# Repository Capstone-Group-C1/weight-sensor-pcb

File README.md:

# weight-sensor-pcb
Converts Load Cell(s) analog signal into CAN signal

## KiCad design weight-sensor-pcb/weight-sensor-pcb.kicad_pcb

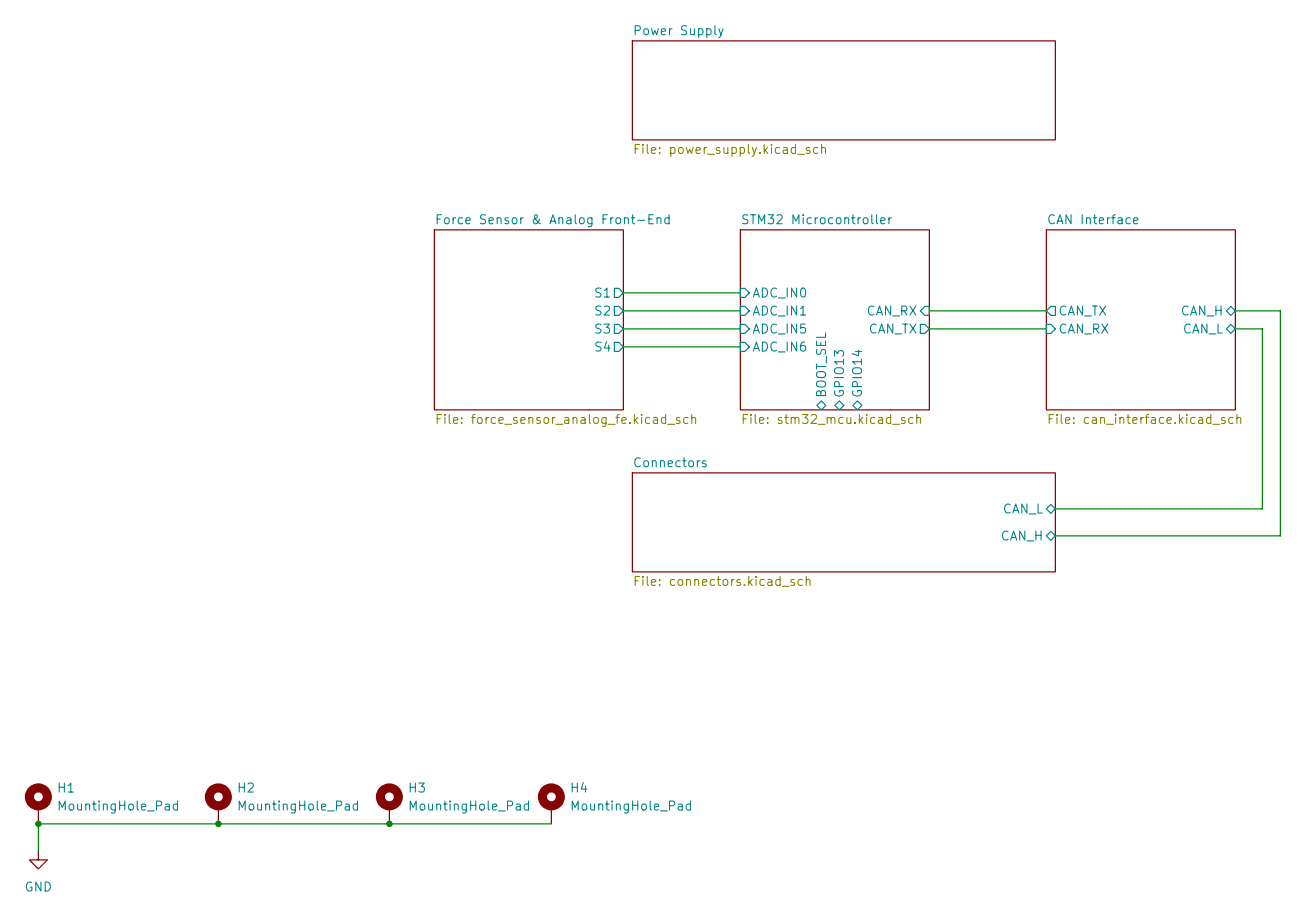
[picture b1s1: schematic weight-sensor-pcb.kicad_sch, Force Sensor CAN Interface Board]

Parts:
H1, H2, H3, H4: MountingHole_Pad; MountingHole_2.2mm_M2_Pad_Via

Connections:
GND: H1.1, H2.1, H3.1, H4.1; also elsewhere on the board

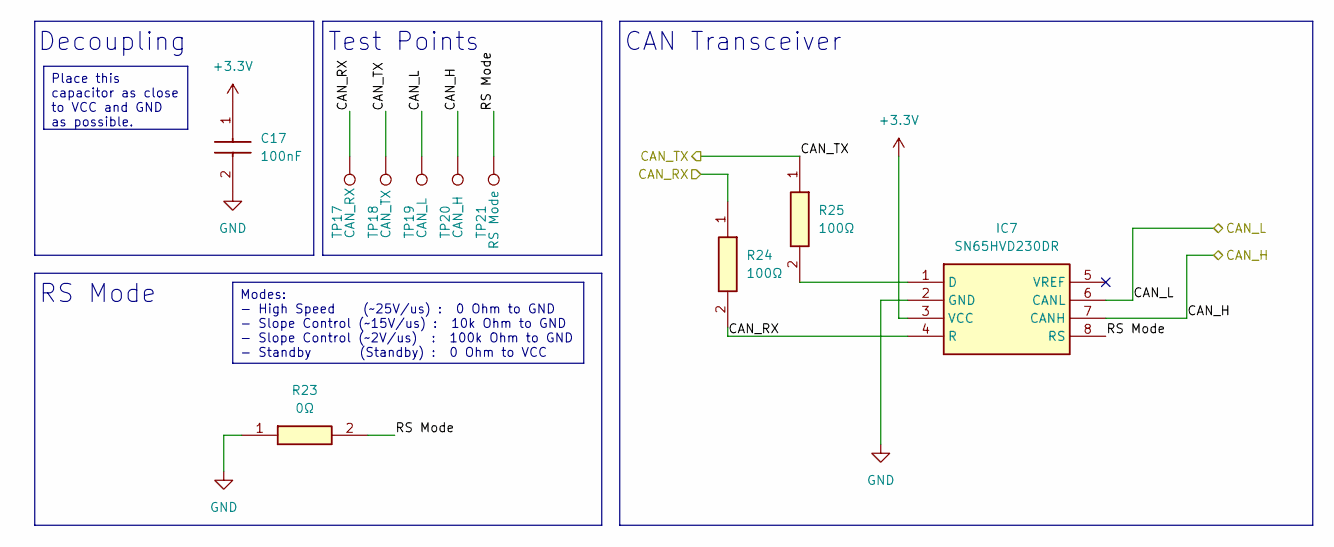
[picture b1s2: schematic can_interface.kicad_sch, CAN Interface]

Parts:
C17: 100nF; CAPC1005X70N; Manufacturer_Part_Number GRM155R70J104KA01D; Mouser Part Number 81-GRM155R70J104KA1D
IC7: SN65HVD230DR; SOT127P600X175-8N; Mouser Part Number 595-SN65HVD230DR
R23: 0Ω; RESC1608X55N; Manufacturer_Part_Number RC0603JR-070RL; Mouser Part Number 603-RC0603JR-070RL
R24, R25: 100Ω; RESC1608X55N; Manufacturer_Part_Number RC0603FR-07100RL; Mouser Part Number 603-RC0603FR-07100RL
TP17: CAN_RX; TestPoint_Pad_D1.5mm
TP18: CAN_TX; TestPoint_Pad_D1.5mm
TP19: CAN_L; TestPoint_Pad_D1.5mm
TP20: CAN_H; TestPoint_Pad_D1.5mm
TP21: RS Mode; TestPoint_Pad_D1.5mm

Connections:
+3.3V: C17.1, IC7.3 (VCC); also elsewhere on the board
/CAN Interface/CAN_H: IC7.7 (CANH), TP20.1; also elsewhere on the board
/CAN Interface/CAN_L: IC7.6 (CANL), TP19.1; also elsewhere on the board
/CAN Interface/CAN_RX: IC7.4 (R), R24.1, R24.2, TP17.1; also elsewhere on the board
/CAN Interface/CAN_TX: R25.1, TP18.1; also elsewhere on the board
/CAN Interface/RS Mode: IC7.8 (RS), R23.2, TP21.1
GND: C17.2, IC7.2 (GND), R23.1; also elsewhere on the board
unnamed: IC7.1 (D), R25.2

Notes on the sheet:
Decoupling
Test Points
CAN Transceiver
RS Mode
Modes: - High Speed (~25V/us) : 0 Ohm to GND - Slope Control (~15V/us) : 10k Ohm to GND - Slope Control (~2V/us) : 100k Ohm to GND - Standby (Standby) : 0 Ohm to VCC
Place this capacitor as close to VCC and GND as possible.

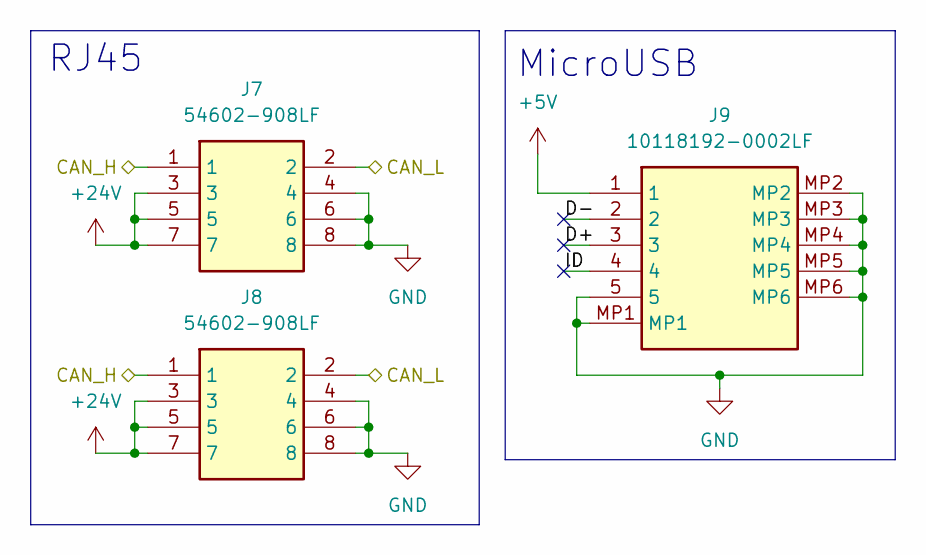
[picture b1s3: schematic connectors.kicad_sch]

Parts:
J7, J8: 54602-908LF; 54602908LF; Manufacturer_Part_Number 54602-908LF
J9: 10118192-0002LF; 101181920002LF; Manufacturer_Part_Number 10118192-0002LF

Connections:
+5V: J9.1; also elsewhere on the board
+24V: J7.3, J7.5, J7.7, J8.3, J8.5, J8.7; also elsewhere on the board
/CAN Interface/CAN_H: J7.1, J8.1; also elsewhere on the board
/CAN Interface/CAN_L: J7.2, J8.2; also elsewhere on the board
/Connectors/D+: J9.3
/Connectors/D-: J9.2
/Connectors/ID: J9.4
GND: J7.4, J7.6, J7.8, J8.4, J8.6, J8.8, J9.5, J9.MP1, J9.MP2, J9.MP3, J9.MP4, J9.MP5, J9.MP6; also elsewhere on the board

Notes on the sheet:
MicroUSB
RJ45

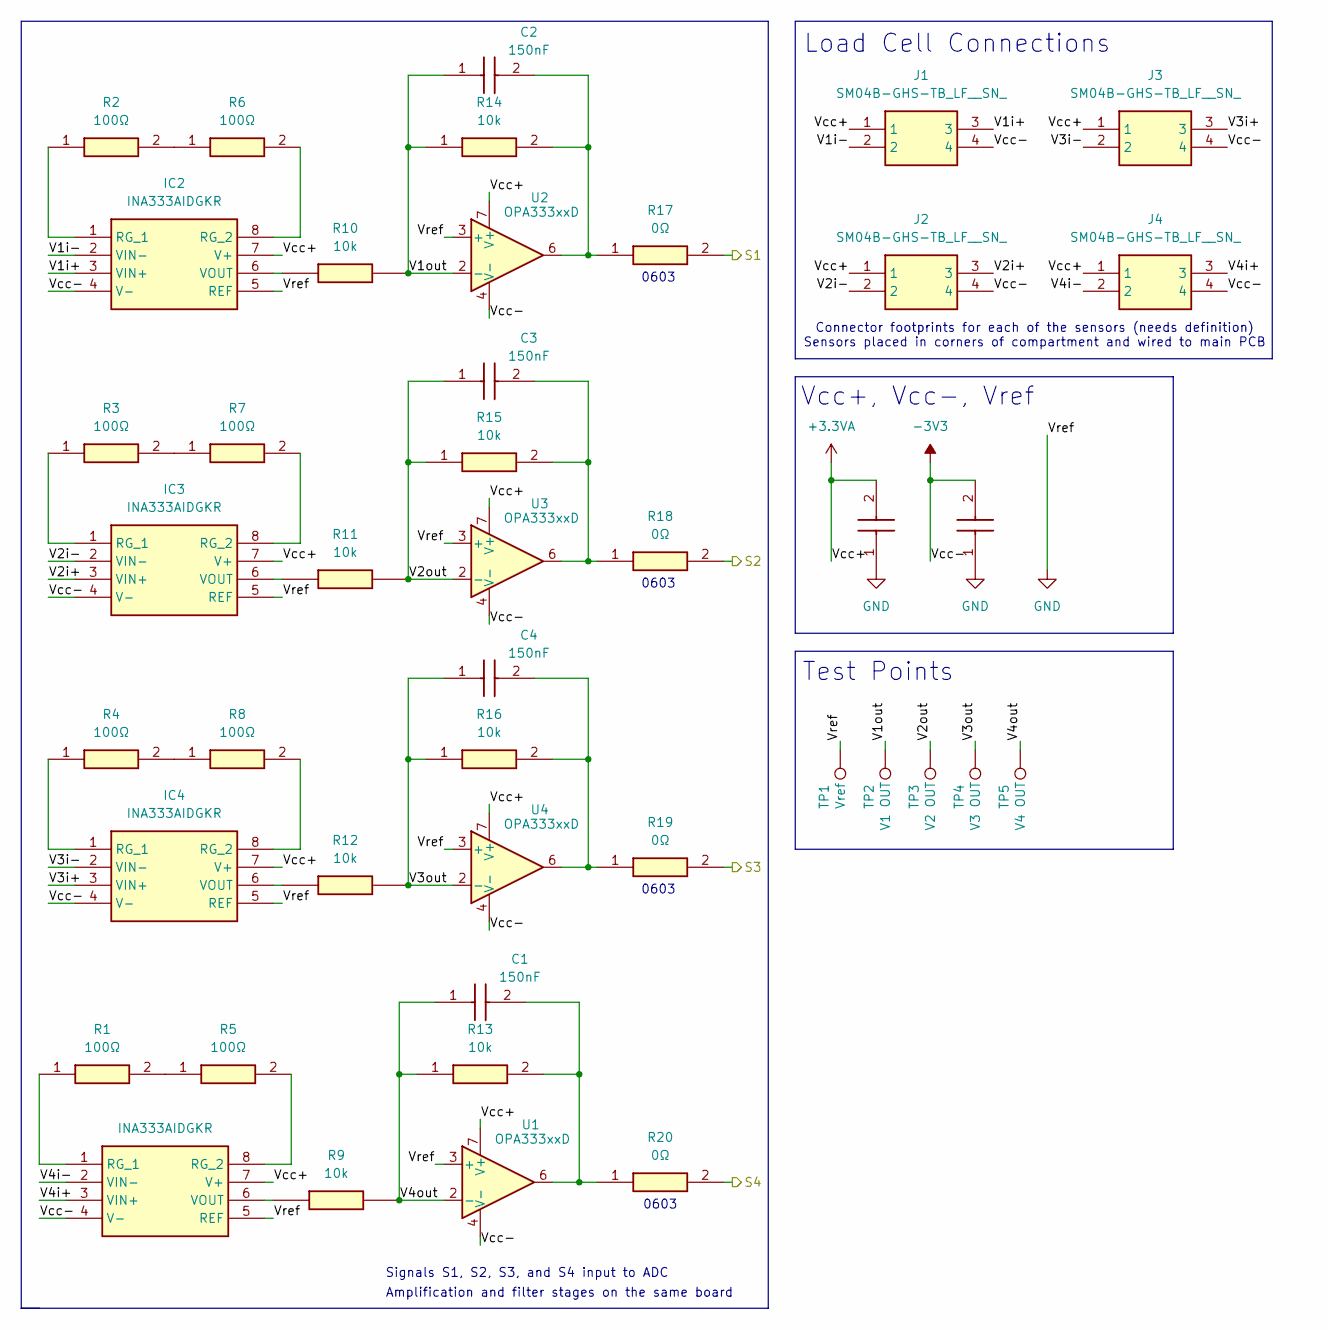
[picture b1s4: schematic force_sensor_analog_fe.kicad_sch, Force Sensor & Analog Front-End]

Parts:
C1, C2, C3, C4: 150nF; C4532_Commercial; Manufacturer_Part_Number C4532C0G1H154J250KA
C5, C6: 0.1uF; CAPC0603X33N; Mouser Part Number 81-GRM33C71C104KE14D
IC1, IC2, IC3, IC4: INA333AIDGKR; SOP65P490X110-8N; Manufacturer_Part_Number INA333AIDGKR; Mouser Part Number 595-INA333AIDGKR
J1, J2, J3, J4: SM04B-GHS-TB_LF__SN_; SM04B-GHS-TB; Mouser Part Number N/A
R1, R2, R3, R4, R5, R6, R7, R8: 100Ω; RESC1608X55N; Manufacturer_Part_Number RC0603FR-07100RL; Mouser Part Number 603-RC0603FR-07100RL
R9, R10, R11, R12, R13, R14, R15, R16: 10k; RESC1608X55N; Manufacturer_Part_Number RMCF0603FT10K0; Mouser Part Number 708-RMCF0603FT10K0
R17, R18, R19, R20: 0Ω; RESC1608X55N; Manufacturer_Part_Number RC0603JR-070RL; Mouser Part Number 603-RC0603JR-070RL
TP1: Vref; TestPoint_Pad_D1.5mm
TP2: V1 OUT; TestPoint_Pad_D1.5mm
TP3: V2 OUT; TestPoint_Pad_D1.5mm
TP4: V3 OUT; TestPoint_Pad_D1.5mm
TP5: V4 OUT; TestPoint_Pad_D1.5mm
U1, U2, U3, U4: OPA333xxD; SOIC-8_3.9x4.9mm_P1.27mm

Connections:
+3.3VA: C5.2, IC1.7 (V+), IC2.7 (V+), IC3.7 (V+), IC4.7 (V+), J1.1, J2.1, J3.1, J4.1, U1.7 (V+), U2.7 (V+), U3.7 (V+), U4.7 (V+); also elsewhere on the board
-3V3: C6.2, IC1.4 (V-), IC2.4 (V-), IC3.4 (V-), IC4.4 (V-), J1.4, J2.4, J3.4, J4.4, U1.4 (V-), U2.4 (V-), U3.4 (V-), U4.4 (V-); also elsewhere on the board
/Force Sensor & Analog Front-End/V1i+: IC2.3 (VIN+), J1.3
/Force Sensor & Analog Front-End/V1i-: IC2.2 (VIN-), J1.2
/Force Sensor & Analog Front-End/V1out: C2.1, R10.2, R14.1, TP2.1, U2.2 (-)
/Force Sensor & Analog Front-End/V2i+: IC3.3 (VIN+), J2.3
/Force Sensor & Analog Front-End/V2i-: IC3.2 (VIN-), J2.2
/Force Sensor & Analog Front-End/V2out: C3.1, R11.2, R15.1, TP3.1, U3.2 (-)
/Force Sensor & Analog Front-End/V3i+: IC4.3 (VIN+), J3.3
/Force Sensor & Analog Front-End/V3i-: IC4.2 (VIN-), J3.2
/Force Sensor & Analog Front-End/V3out: C4.1, R12.2, R16.1, TP4.1, U4.2 (-)
/Force Sensor & Analog Front-End/V4i+: IC1.3 (VIN+), J4.3
/Force Sensor & Analog Front-End/V4i-: IC1.2 (VIN-), J4.2
/Force Sensor & Analog Front-End/V4out: C1.1, R9.2, R13.1, TP5.1, U1.2 (-)
/STM32 Microcontroller/ADC_IN0: R17.2; also elsewhere on the board
/STM32 Microcontroller/ADC_IN1: R18.2; also elsewhere on the board
/STM32 Microcontroller/ADC_IN5: R19.2; also elsewhere on the board
/STM32 Microcontroller/ADC_IN6: R20.2; also elsewhere on the board
GND: C5.1, C6.1, IC1.5 (REF), IC2.5 (REF), IC3.5 (REF), IC4.5 (REF), TP1.1, U1.3 (+), U2.3 (+), U3.3 (+), U4.3 (+); also elsewhere on the board
unnamed: C1.2, R13.2, R20.1, U1.6
unnamed: C2.2, R14.2, R17.1, U2.6
unnamed: C3.2, R15.2, R18.1, U3.6
unnamed: C4.2, R16.2, R19.1, U4.6
unnamed: IC1.1 (RG_1), R1.1
unnamed: IC1.8 (RG_2), R5.2
unnamed: IC1.6 (VOUT), R9.1
unnamed: IC2.1 (RG_1), R2.1
unnamed: IC2.8 (RG_2), R6.2
unnamed: IC2.6 (VOUT), R10.1
unnamed: IC3.1 (RG_1), R3.1
unnamed: IC3.8 (RG_2), R7.2
unnamed: IC3.6 (VOUT), R11.1
unnamed: IC4.1 (RG_1), R4.1
unnamed: IC4.8 (RG_2), R8.2
unnamed: IC4.6 (VOUT), R12.1
unnamed: R1.2, R5.1
unnamed: R2.2, R6.1
unnamed: R3.2, R7.1
unnamed: R4.2, R8.1

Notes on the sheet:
Load Cell Connections
0603
Signals S1, S2, S3, and S4 input to ADC
Amplification and filter stages on the same board
Connector footprints for each of the sensors (needs definition) Sensors placed in corners of compartment and wired to main PCB
Test Points
Vcc+, Vcc-, Vref

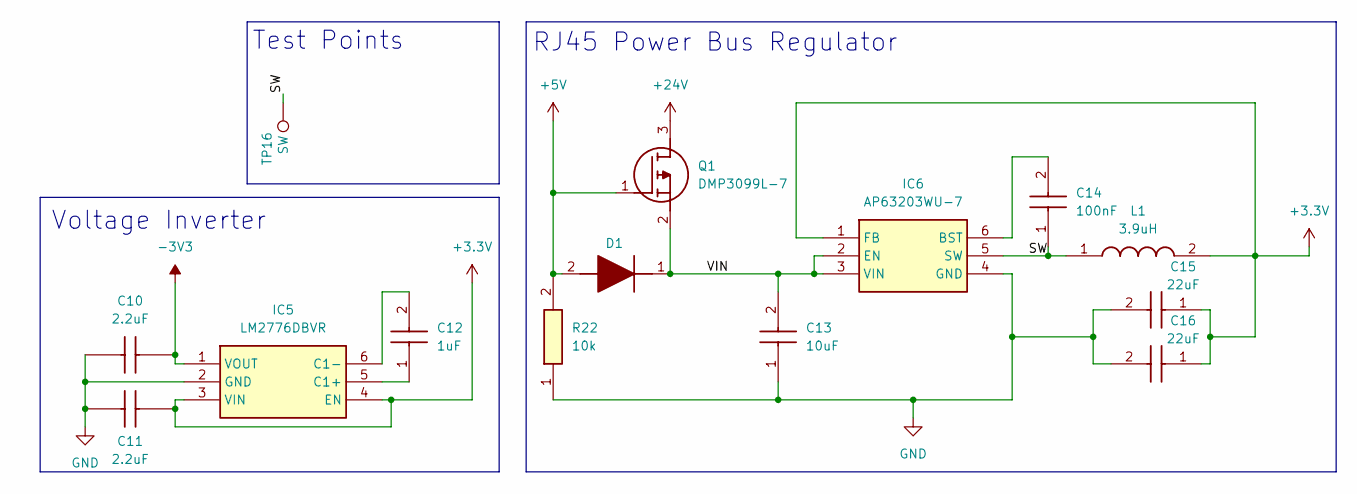
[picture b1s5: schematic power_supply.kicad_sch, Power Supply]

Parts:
C10, C11: 2.2uF; CAPC1608X90N; Mouser Part Number 81-GRM1885C1H222JA01
C12: 1uF; CAPC1005X70N; Manufacturer_Part_Number GRM155R70J105KA12D; Mouser Part Number 81-GRM155R70J105KA2D
C13: 10uF; CAPC2012X145N; Mouser Part Number 81-GRM21BR61E106KA3K
C14: 100nF; CAPC1005X70N; Manufacturer_Part_Number GRM155R70J104KA01D; Mouser Part Number 81-GRM155R70J104KA1D
C15, C16: 22uF; CAPC3216X190N; Mouser Part Number 963-TMK316BBJ226ML-T
D1: BAT30KFILM; SODFL1608X70N; Manufacturer_Part_Number BAT30KFILM; Mouser Part Number 511-BAT30KFILM
IC5: LM2776DBVR; SOT95P280X145-6N; Manufacturer_Part_Number LM2776DBVR; Mouser Part Number 595-LM2776DBVR
IC6: AP63203WU-7; AP63203WU7; Manufacturer_Part_Number AP63203WU-7; Mouser Part Number 621-AP63203WU-7
L1: 3.9uH; ASPI0628150MT1; Mouser Part Number 815-ASPI-0628-3R9MT1
Q1: DMP3099L-7; SOT96P240X115-3N; Manufacturer_Part_Number DMP3099L-7; Mouser Part Number 621-DMP3099L-7
R22: 10k; RESC1608X55N; Manufacturer_Part_Number RMCF0603FT10K0; Mouser Part Number 708-RMCF0603FT10K0
TP16: SW; TestPoint_Pad_D1.5mm

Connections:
+3.3V: C11.1, C15.1, C16.1, IC5.3 (VIN), IC5.4 (EN), IC6.1 (FB), L1.2; also elsewhere on the board
+5V: D1.2 (A), Q1.1 (G), R22.2; also elsewhere on the board
+24V: Q1.3 (D); also elsewhere on the board
-3V3: C10.1, IC5.1 (VOUT); also elsewhere on the board
/Power Supply/SW: C14.1, IC6.5 (SW), L1.1, TP16.1
/Power Supply/VIN: C13.2, D1.1 (K), IC6.2 (EN), IC6.3 (VIN), Q1.2 (S)
GND: C10.2, C11.2, C13.1, C15.2, C16.2, IC5.2 (GND), IC6.4 (GND), R22.1; also elsewhere on the board
unnamed: C12.1, IC5.5 (C1+)
unnamed: C12.2, IC5.6 (C1-)
unnamed: C14.2, IC6.6 (BST)

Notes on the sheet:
RJ45 Power Bus Regulator
Test Points
Voltage Inverter

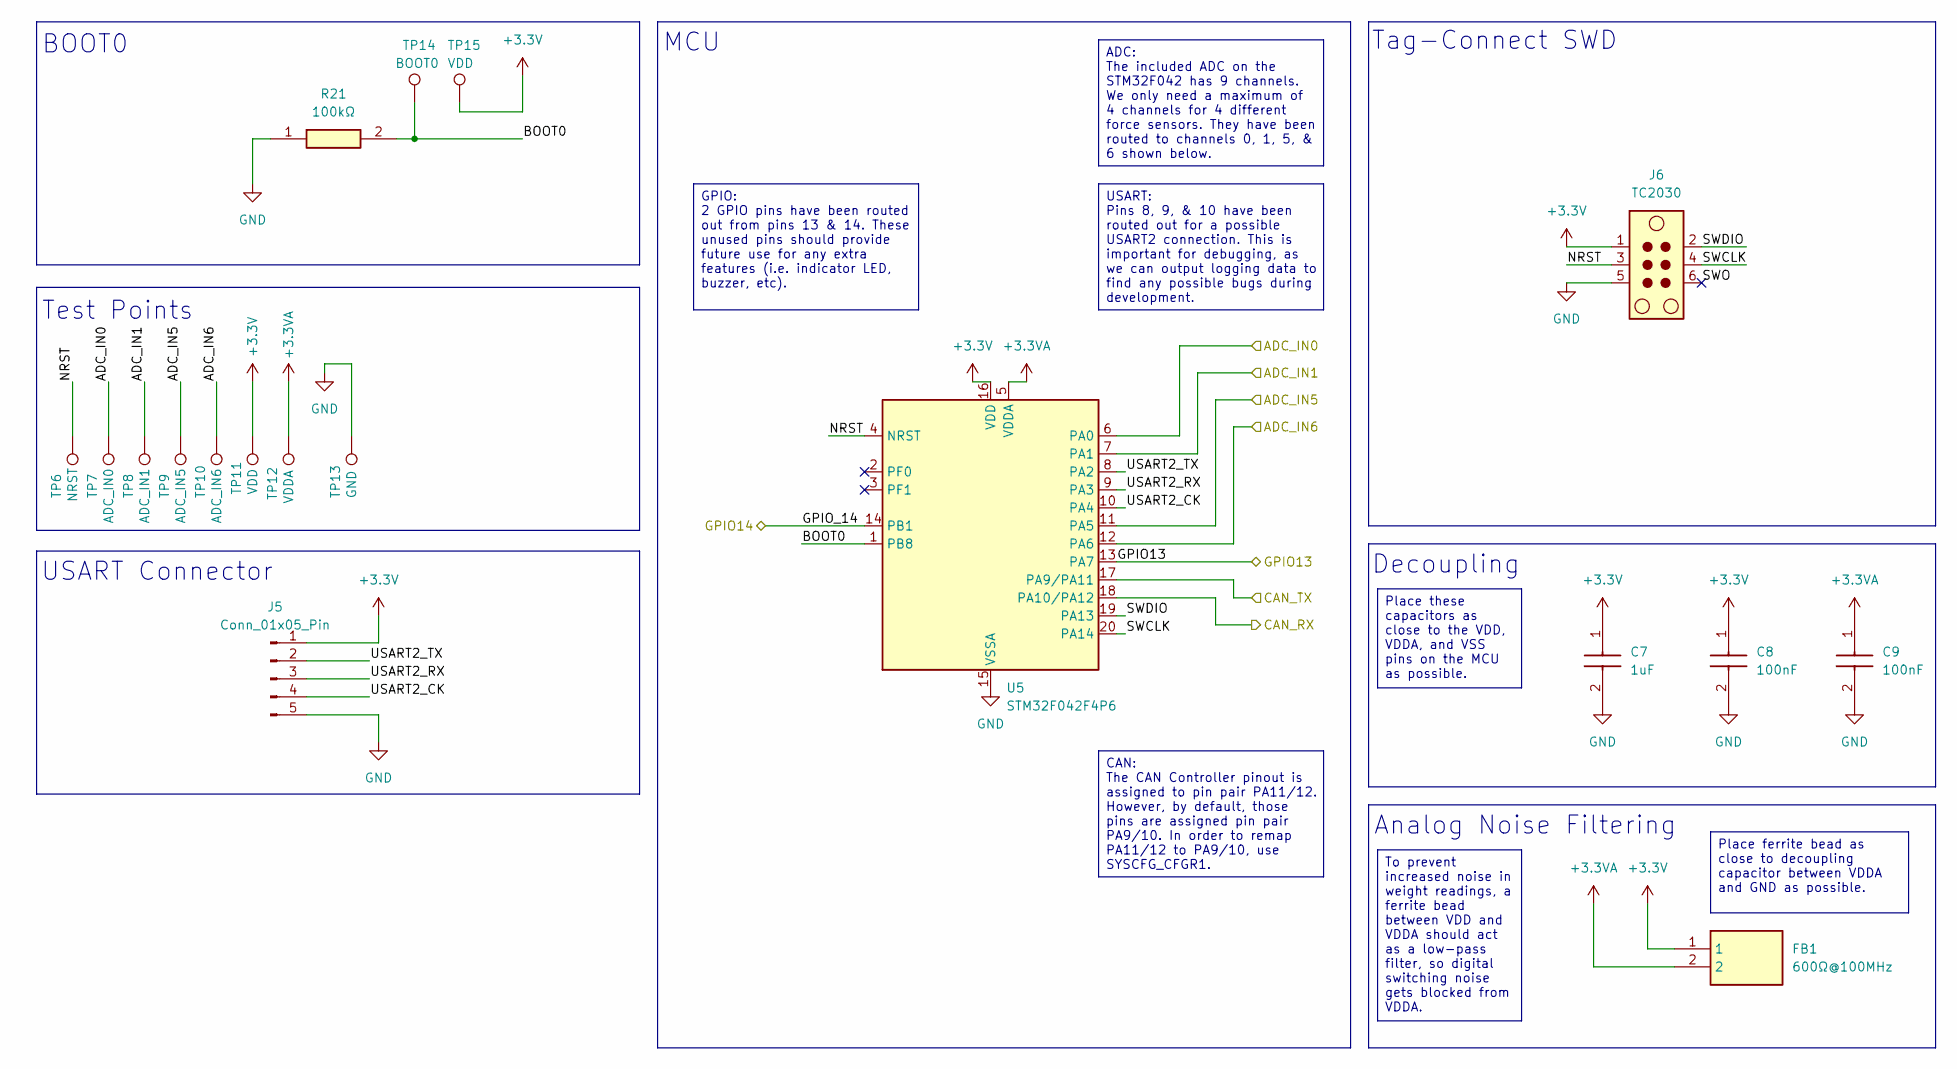
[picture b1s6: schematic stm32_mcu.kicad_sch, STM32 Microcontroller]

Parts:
C7: 1uF; CAPC1005X70N; Manufacturer_Part_Number GRM155R70J105KA12D; Mouser Part Number 81-GRM155R70J105KA2D
C8, C9: 100nF; CAPC1005X70N; Manufacturer_Part_Number GRM155R70J104KA01D; Mouser Part Number 81-GRM155R70J104KA1D
FB1: 600Ω@100MHz; NFZ15SG152SN10B; Manufacturer_Part_Number BLM15AG601SN1D; Mouser Part Number 81-BLM15AG601SN1D
J5: Conn_01x05_Pin; PinHeader_1x05_P1.27mm_Vertical
J6: TC2030; Tag-Connect_TC2030-IDC-NL_2x03_P1.27mm_Vertical
R21: 100kΩ; RESC1005X40N; Manufacturer_Part_Number RC0402FR-07100KL
TP6: NRST; TestPoint_Pad_D1.5mm
TP7: ADC_IN0; TestPoint_Pad_D1.5mm
TP8: ADC_IN1; TestPoint_Pad_D1.5mm
TP9: ADC_IN5; TestPoint_Pad_D1.5mm
TP10: ADC_IN6; TestPoint_Pad_D1.5mm
TP11, TP15: VDD; TestPoint_Pad_D1.5mm
TP12: VDDA; TestPoint_Pad_D1.5mm
TP13: GND; TestPoint_Pad_D1.5mm
TP14: BOOT0; TestPoint_Pad_D1.5mm
U5: STM32F042F4P6; TSSOP-20_4.4x6.5mm_P0.65mm

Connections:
+3.3V: C7.1, C8.1, FB1.1, J5.1, J6.1, TP11.1, TP15.1, U5.16 (VDD); also elsewhere on the board
+3.3VA: C9.1, FB1.2, TP12.1, U5.5 (VDDA); also elsewhere on the board
/CAN Interface/CAN_RX: U5.17 (PA9/PA11); also elsewhere on the board
/CAN Interface/CAN_TX: U5.18 (PA10/PA12); also elsewhere on the board
/STM32 Microcontroller/ADC_IN0: TP7.1, U5.6 (PA0); also elsewhere on the board
/STM32 Microcontroller/ADC_IN1: TP8.1, U5.7 (PA1); also elsewhere on the board
/STM32 Microcontroller/ADC_IN5: TP9.1, U5.11 (PA5); also elsewhere on the board
/STM32 Microcontroller/ADC_IN6: TP10.1, U5.12 (PA6); also elsewhere on the board
/STM32 Microcontroller/BOOT0: R21.2, TP14.1, U5.1 (PB8)
/STM32 Microcontroller/GPIO13: U5.13 (PA7)
/STM32 Microcontroller/GPIO_14: U5.14 (PB1)
/STM32 Microcontroller/NRST: J6.3, TP6.1, U5.4 (NRST)
/STM32 Microcontroller/SWCLK: J6.4, U5.20 (PA14)
/STM32 Microcontroller/SWDIO: J6.2, U5.19 (PA13)
/STM32 Microcontroller/SWO: J6.6
/STM32 Microcontroller/USART2_CK: J5.4, U5.10 (PA4)
/STM32 Microcontroller/USART2_RX: J5.3, U5.9 (PA3)
/STM32 Microcontroller/USART2_TX: J5.2, U5.8 (PA2)
GND: C7.2, C8.2, C9.2, J5.5, J6.5, R21.1, TP13.1, U5.15 (VSSA); also elsewhere on the board

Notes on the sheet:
Analog Noise Filtering
Test Points
MCU
BOOT0
USART Connector
Decoupling
Tag-Connect SWD
ADC: The included ADC on the STM32F042 has 9 channels. We only need a maximum of 4 channels for 4 different force sensors. They have been routed to channels 0, 1, 5, & 6 shown below.
Place these capacitors as close to the VDD, VDDA, and VSS pins on the MCU as possible.
USART: Pins 8, 9, & 10 have been routed out for a possible USART2 connection. This is important for debugging, as we can output logging data to find any possible bugs during development.
GPIO: 2 GPIO pins have been routed out from pins 13 & 14. These unused pins should provide future use for any extra features (i.e. indicator LED, buzzer, etc).
CAN: The CAN Controller pinout is assigned to pin pair PA11/12. However, by default, those pins are assigned pin pair PA9/10. In order to remap PA11/12 to PA9/10, use SYSCFG_CFGR1.
To prevent increased noise in weight readings, a ferrite bead between VDD and VDDA should act as a low-pass filter, so digital switching noise gets blocked from VDDA.
Place ferrite bead as close to decoupling capacitor between VDDA and GND as possible.

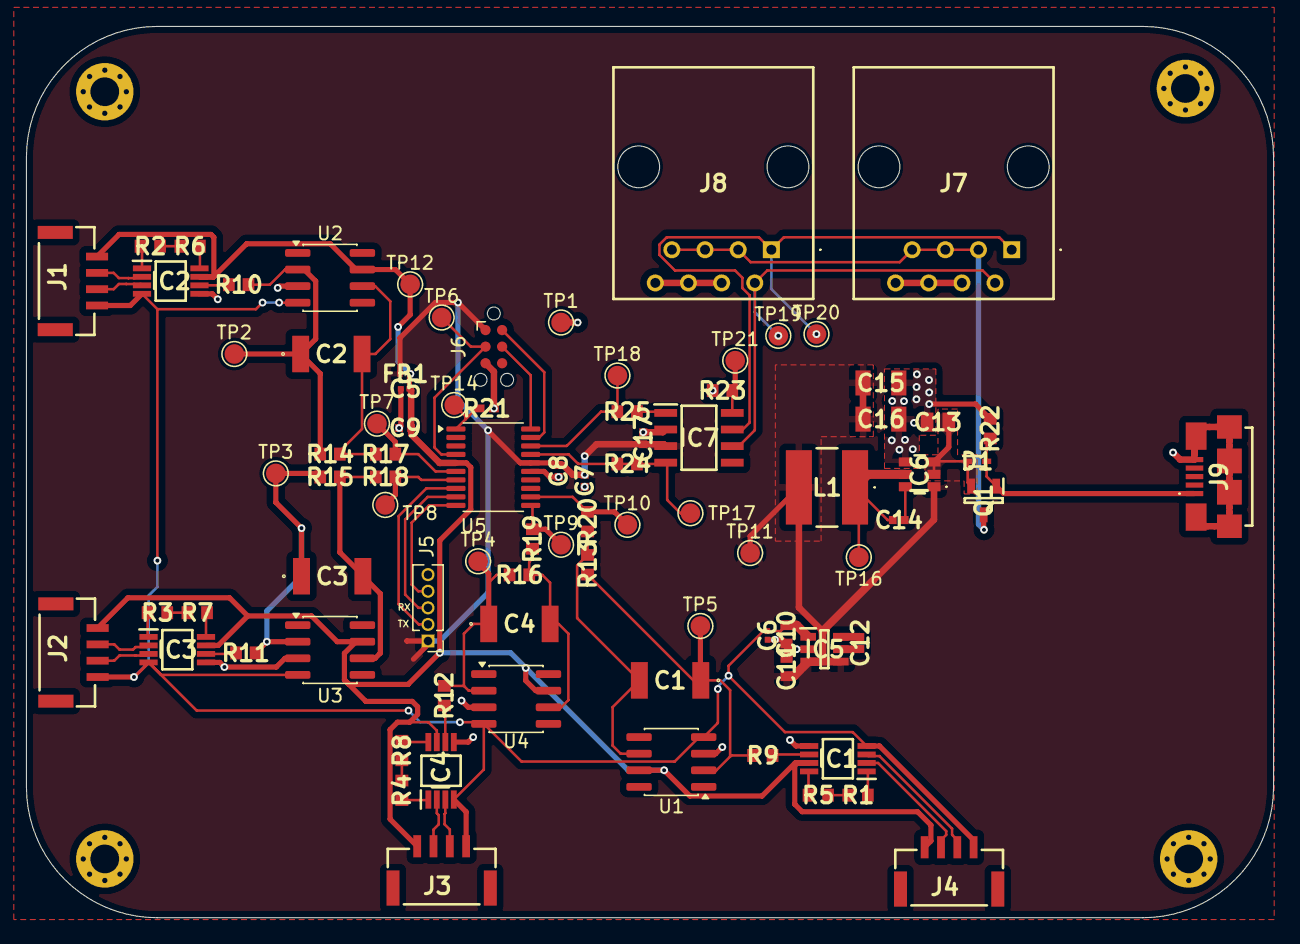
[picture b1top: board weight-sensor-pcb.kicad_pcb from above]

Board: 2 copper layers, 95.5 x 68.2 mm, 90 parts (0 on the bottom side), 60 nets.

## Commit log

2025-12-21 attempt at force sensor & analog front end schematic
2025-12-31 Swap MCU, add Library Loader integration
2026-01-28 Add SamacSys Addon
2026-01-28 Add Serial Connection and CAN Transceiver
2026-01-29 Add hierarchial labels to MCU and CAN Interface sheets
2026-01-29 updated tag-connect SWD schematic symbol
2026-02-02 Add decoupling capacitors, current limiting resistors for MCU and CAN Transceiver
2026-02-03 Add ferrite bead between VDDA and VDD, add more notes for MCU
2026-02-03 Add Test points, CAN connector, USART connector
2026-02-05 test
2026-02-05 Transfered LTSpice analog schematic to its appropriate schematic page
2026-02-18 initial PCB layout design
2026-02-18 schematic clean up
2026-02-18 further schematic clean up
2026-02-18 git commit
2026-02-18 update CAN transceiver schematic/layout, use env vars for library paths
2026-02-23 message
2026-02-24 finish converter schematic
2026-03-04 Add backup USB power
2026-03-09 Add new buck regulator (no component values)
2026-03-10 update new buck regulator schematic
2026-03-10 Add parts to use in 3.3v buck regulator
2026-03-10 replace generic components with specific components
2026-03-10 replace generic feedback resistors with specific components
2026-03-10 add more specific components
2026-03-11 started layout
2026-03-11 layout progress 1
2026-03-11 more layout updates, add mounting hole pads to schematic
2026-03-11 Layout draft complete
